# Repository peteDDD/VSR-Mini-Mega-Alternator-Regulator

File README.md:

# VSR-Mini-Mega-Rev-1

This project is a refactoring of the amazing work of William A. Thomason ("Al") to create an open source very smart alternator regulator.  That work can be seen here:
http://arduinoalternatorregulator.blogspot.com/

That open-source hardware is no longer orderable through Al.  In January 2019, that product "went pro" and is now available as a commercial product as you can see here:
http://wakespeed.com/products.html

In December 2020 I began refactoring Al's code to remove CAN and Bluetooth related code and move the hardware to a new PC board with a Mini Mega Pro 2560 daughter card
as the processor. Thus "VSR MINI MEGA" was born.

I wanted to remove some functionality and add other functionality.  Also, moving to the Mini Mega Pro 2560 provided more memory for expansion.

New hardware features include:
  - Dual INA226 current voltage sensors (for Alternator and Battery)    * Al's designs supported a second shunt but required a separate battery monitor to implement 
      that very unique and powerful functionality.  THe VSR MINI MEGA directly support two shunts.
  - Three Feature-in Ports and Three Feature-out Ports (functionality and port assignments selectable in Config.h)  
  - Two serial port screw headers, separate from port used to USB programming, one can support external full function display 
       (A remote display based on an Arduino Uno and a TFT color display will be published in the near future)
  - Two I2C pin headers to add an in-case OLED display or other features
  - Red and green LED output connections (independent of the Feature-out option which preceeded it).  
 
New firmware features include, selectable and configurable in Config.h include  :  
  - ENABLE_FEATURE_IN_SCUBA  - uses one of the Feature-in ports to shift the alternator field PWM way down so a small engine can run a SCUBA compressor while maintaining a 
      bit of output for keeping up with an electric clutch and relays used by the SCUBA compressor.
 -  FEATURE_OUT_GREEN_LED, FEATURE_OUT_RED_LED - echo the red and green status LED to your choice of Feature-out ports.
 -  FEATURE_OUT_LIFEPO_SHUTDOWN_ALARM - provides a Feature-out alarm which follows the Force-o-Float Feature-in
 -  USE_OLED - provides a class-based OLED display which displays realtime alternator and battery voltage, current, and temperatures, field PWM, current charging mode, 
      time in that mode, flags like "Forced Float" and "SCUBA", and error messages.  The display also reflects the DIP switch settings in human-speak at boot up.
 -  USE_SERIAL_DISPLAY - supports Arduio Uno-based color TFT display which alternately displays a screen showing alternator amps and battery voltage and a graphical display
      of the actual charging curve (amps and volts) over time
      
Features and firmware removed include (as best I can so far)
 -  CAN support
 -  Bluetooth artifacts from earlier VSR versions
 -  Engine control artifacts from Al's 6HP 12V diesel genset/water maker which preceded the VSR alternator regulator.
 -  Remote battery monitor artifacts
 
Future (near-term) enhancements planned:
 -  There is a stub in this release to support monitoring LiFePO4 battery management system's output for a pending battery disconnect.  This will then trigger a "Force-to-float"
      on the Mini-Mega to protect the alternator from a battery disconnect.
      
Also developed:
 -  Bench testing board to mimic battery and alternator voltages, currents, and temperatures, and feature-in and feature-out functions (switches and LEDs respectively)  
      This board also can have small volt and current meters on it and bannana jacks for stator input (from a signal generator) and tach out (to a frequency counter or 
      oscilloscope.
 -  The previously-mentioned remote color graphical display
 -  3D-printed case for VSR Mega-Mini with 0.93" OLED
 -  3D-printed bezel for the remote color graphical display

 FULL REFERENCE MANUAL CAN BE FOUND IN THE DOCUMENTATION DIRECTORY.
 
 ###

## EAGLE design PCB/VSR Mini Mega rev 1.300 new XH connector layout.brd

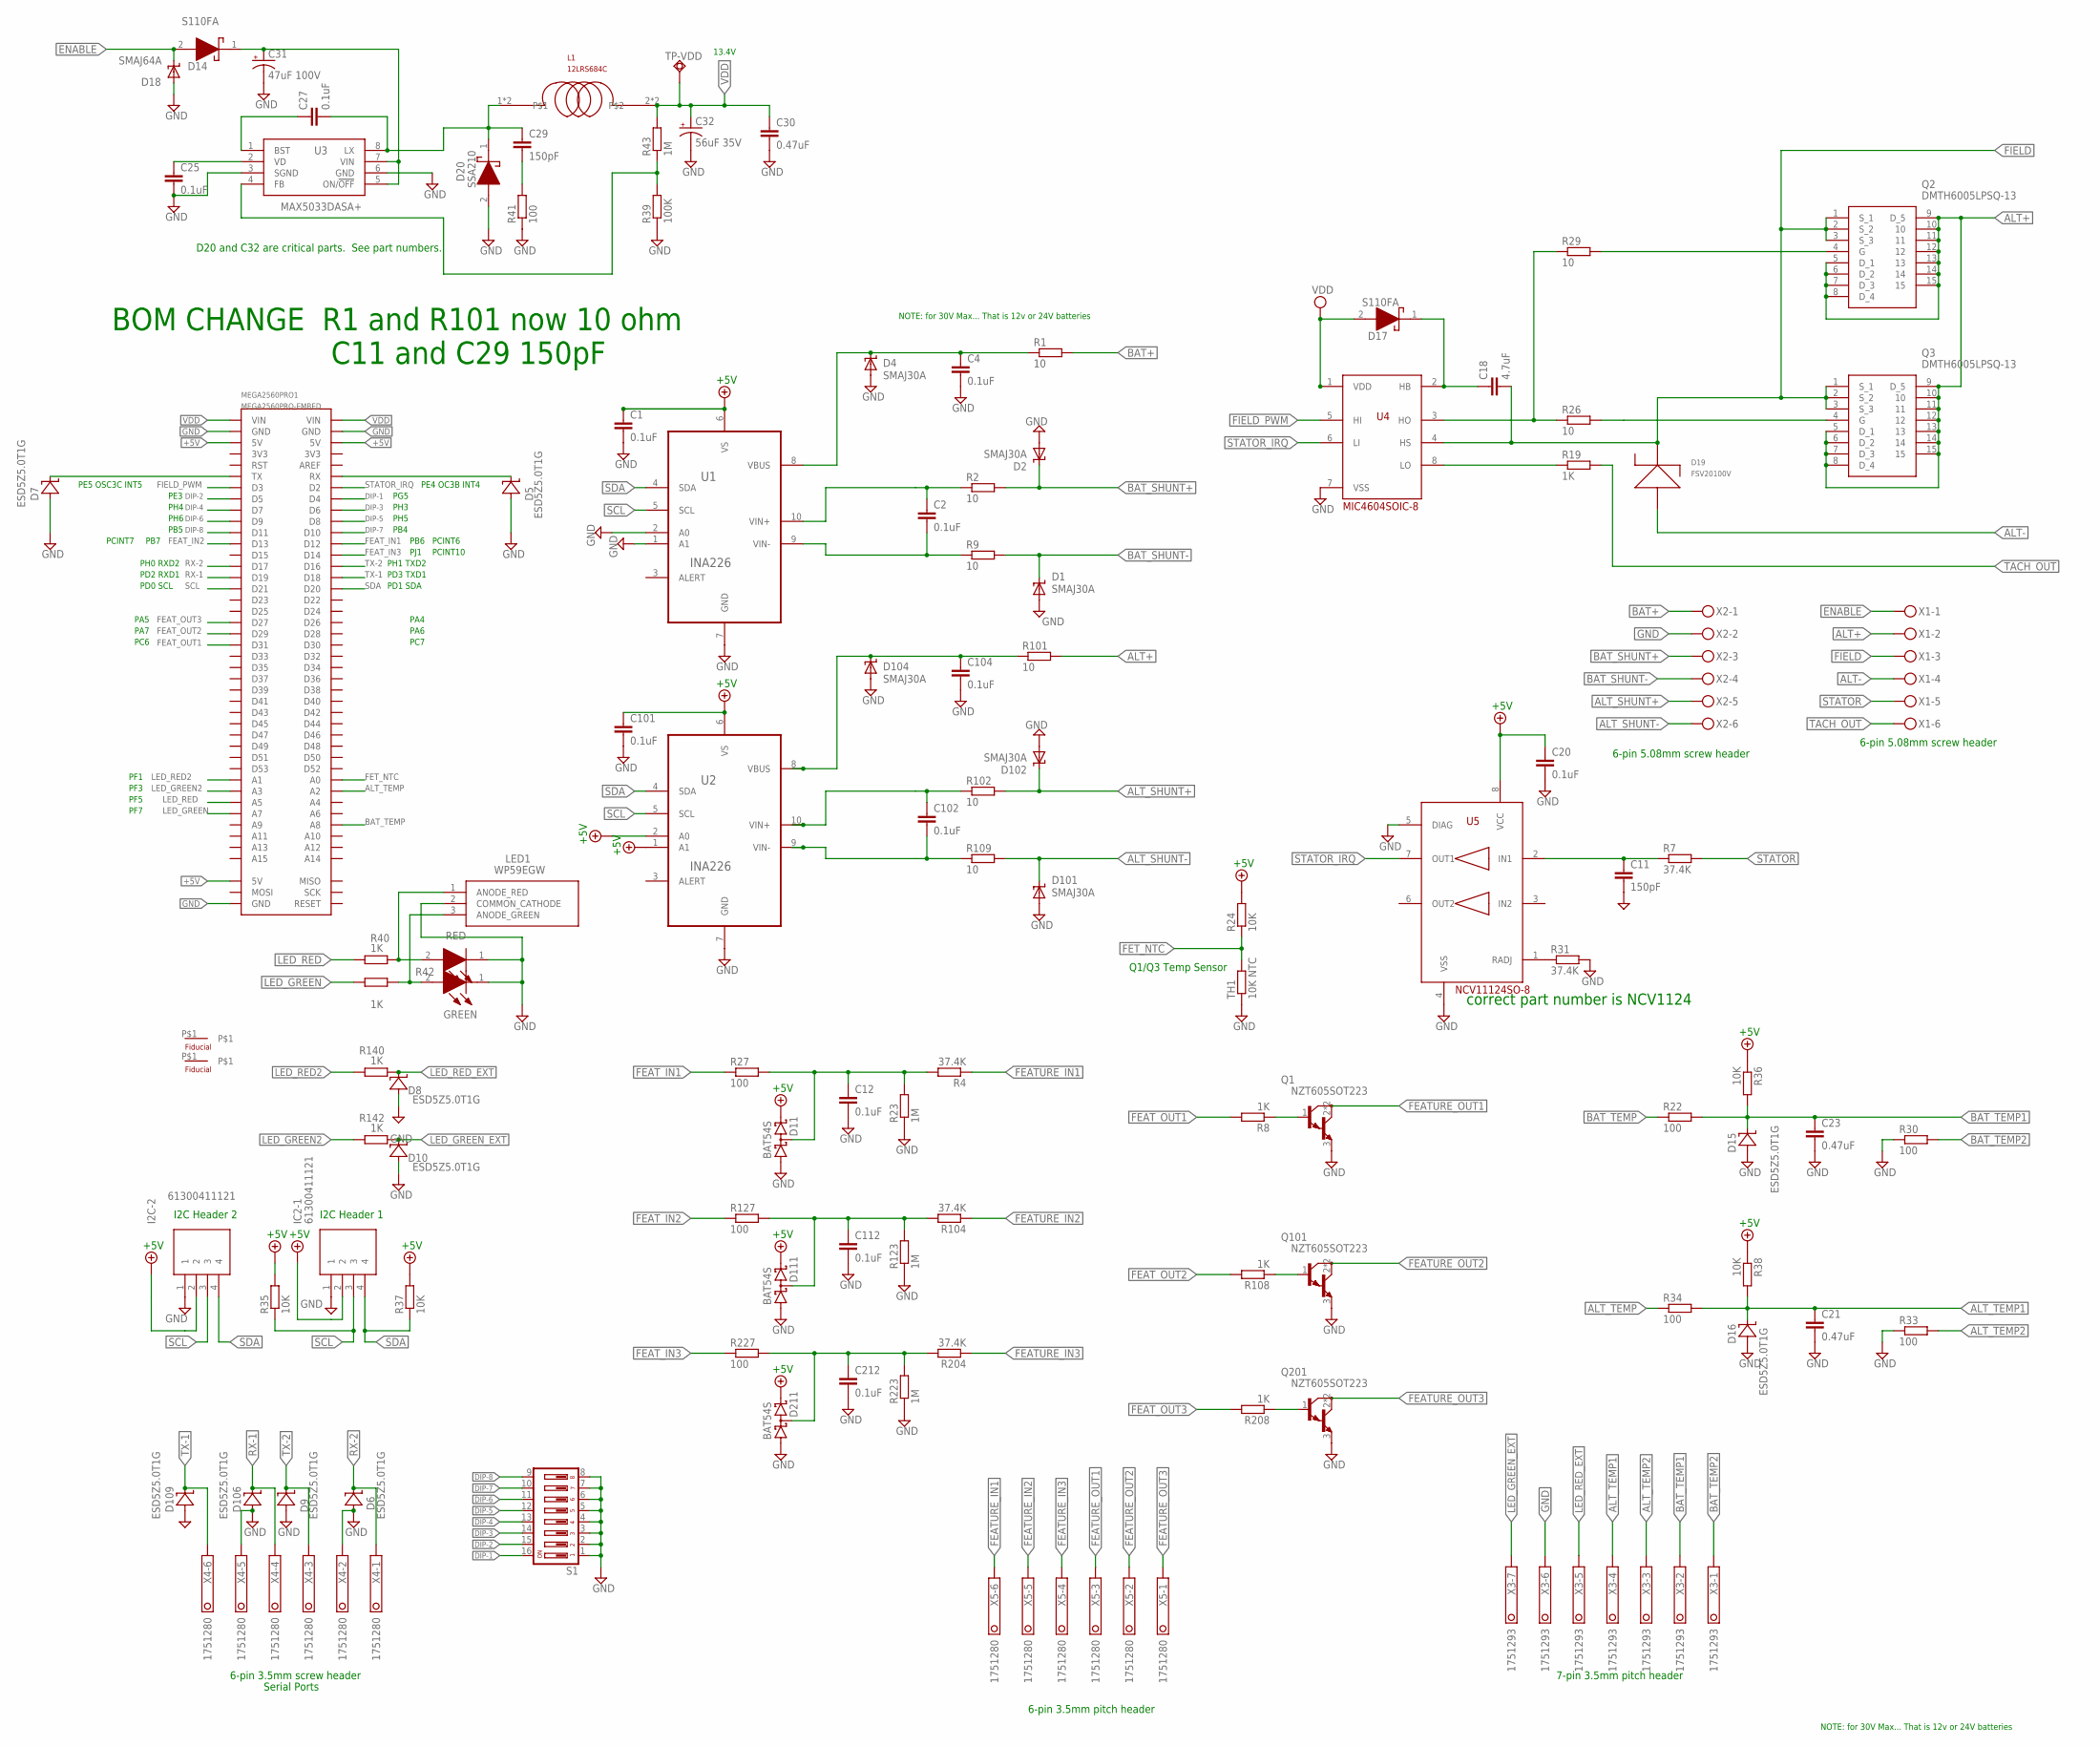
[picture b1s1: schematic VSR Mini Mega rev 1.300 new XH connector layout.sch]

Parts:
C1, C2, C4, C12, C20, C25, C27, C101, C102, C104, C112, C212: 0.1uF; C0603
C11, C29: 150pF; C0603
C18: 4.7uF; C0603K
C21, C23, C30: 0.47uF; C0603
C31: 47uF 100V; CAPPRD500W60D1000H1250B
C32: 56uF 35V; CAPPRD250W50D630H1100B
D1, D2, D4, D101, D102, D104: SMAJ30A; SMBJ
D5, D6, D7, D8, D9, D10, D15, D16, D106, D109: ESD5Z5.0T1G; SOD523
D11, D111, D211: BAT54S; SOT23
D14, D17: S110FA; SODFL3618X143N
D18: SMAJ64A; SMBJ
D19: FSV20100V; TO-277
D20: SSA210; DIOM5227X270N
FIDUCIAL1, FIDUCIAL2: FIDUCIAL060
GREEN: 599-0110-007F; LEDM2012X90N
I2C-2: 61300411121; HDRV4W95P0X254_1X4_1016X254X85
IC2-1: 61300411121; HDRV4W95P0X254_1X4_1016X254X85
L1: 12LRS684C; IND_12LRS156C
LED1: WP59EGW; T-1_3/4(5MM)_BI-COLOR_INDICATO
MEGA2560PRO1: MEGA2560PRO-EMBED
Q1, Q101, Q201: NZT605SOT223; SOT223
Q2, Q3: DMTH6005LPSQ-13; DMTH6005LPSQ13
R1, R2, R9, R26, R29, R101, R102, R109: 10; R0603
R4, R7, R31, R104, R204: 37.4K; R0603
R8, R19, R40, R42, R108, R140, R142, R208: 1K; R0603
R22, R27, R30, R33, R34, R41, R127, R227: 100; R0603
R23, R43, R123, R223: 1M; R0603
R24, R35, R36, R37, R38: 10K; R0603
R39: 100K; R0603
RED: 599-0110-007F; LEDM2012X90N
S1: DP08; DP-08
TH1: 10K NTC; R0402
TP-VDD: TPSQTP20SQ; TP20SQ
U1, U2: INA226; SOP50P490X110-10N
U3: MAX5033DASA+; SOIC127P600X175-8N
U4: MIC4604SOIC-8; SOIC8
U5: NCV11124SO-8; SO-8
X1, X2: MKDSN1,5/6-5,08
X3: 1751293
X4, X5: 1751280

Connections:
+5V: C1.1, C20.1, C101.1, D11.2 (C2), D111.2 (C2), D211.2 (C2), I2C-2.2, IC2-1.2, MEGA2560PRO1.5V@1 (5V), MEGA2560PRO1.5V@2 (5V), MEGA2560PRO1.5V@3 (5V), R24.2, R35.2, R36.1, R37.2, R38.1, U1.6 (VS), U2.1 (A1), U2.2 (A0), U2.6 (VS), U5.8 (VCC)
ALT+: Q2.5 (D_1), Q2.6 (D_2), Q2.7 (D_3), Q2.8 (D_4), Q2.9 (D_5), Q2.10, Q2.11, Q2.12, Q2.13, Q2.14, Q2.15, Q3.5 (D_1), Q3.6 (D_2), Q3.7 (D_3), Q3.8 (D_4), Q3.9 (D_5), Q3.10, Q3.11, Q3.12, Q3.13, Q3.14, Q3.15, R101.2, X1.2
ALT-: D19.1, D19.2, X1.4
ALT_SHUNT+: D102.C, R102.2, X2.5
ALT_SHUNT-: D101.C, R109.2, X2.6
ALT_TEMP: MEGA2560PRO1.A2, R34.1
ALT_TEMP1: C21.1, D16.C, R34.2, R38.2, X3.4
ALT_TEMP2: R33.2, X3.3
BAT+: R1.2, X2.1
BAT_SHUNT+: D2.C, R2.2, X2.3
BAT_SHUNT-: D1.C, R9.2, X2.4
BAT_TEMP: MEGA2560PRO1.A8, R22.1
BAT_TEMP1: C23.1, D15.C, R22.2, R36.2, X3.2
BAT_TEMP2: R30.2, X3.1
D111: C112.1, D111.3 (C1A2), R104.2, R123.2, R127.2
DIP-1: MEGA2560PRO1.D4, S1.16
DIP-2: MEGA2560PRO1.D5, S1.15
DIP-3: MEGA2560PRO1.D6, S1.14
DIP-4: MEGA2560PRO1.D7, S1.13
DIP-5: MEGA2560PRO1.D8, S1.12
DIP-6: MEGA2560PRO1.D9, S1.11
DIP-7: MEGA2560PRO1.D10, S1.10
DIP-8: MEGA2560PRO1.D11, S1.9
ENABLE: D14.2 (A), D18.C, X1.1
FEATURE_IN1: R4.1, X5.6
FEATURE_IN2: R104.1, X5.5
FEATURE_IN3: R204.1, X5.4
FEATURE_OUT1: Q1.2 (C), Q1.4 (C), X5.3
FEATURE_OUT2: Q101.2 (C), Q101.4 (C), X5.2
FEATURE_OUT3: Q201.2 (C), Q201.4 (C), X5.1
FEAT_IN1: MEGA2560PRO1.D12, R27.1
FEAT_IN2: MEGA2560PRO1.D13, R127.1
FEAT_IN3: MEGA2560PRO1.D14, R227.1
FEAT_OUT1: MEGA2560PRO1.D31, R8.2
FEAT_OUT2: MEGA2560PRO1.D29, R108.2
FEAT_OUT3: MEGA2560PRO1.D27, R208.2
FET_NTC: MEGA2560PRO1.A0, R24.1, TH1.2
FIELD: C18.2, D19.3, Q2.1 (S_1), Q2.2 (S_2), Q2.3 (S_3), Q3.1 (S_1), Q3.2 (S_2), Q3.3 (S_3), U4.4 (HS), X1.3
FIELD_PWM: MEGA2560PRO1.D3, U4.5 (HI)
GND: C1.2, C4.2, C11.2, C12.2, C20.2, C21.2, C23.2, C25.2, C30.2, C31.2 (-), C32.2 (-), C101.2, C104.2, C112.2, C212.2, D1.A, D2.A, D4.A, D5.A, D6.A, D7.A, D8.A, D9.A, D10.A, D11.1 (A1), D15.A, D16.A, D18.A, D20.2 (A), D101.A, D102.A, D104.A, D106.A, D109.A, D111.1 (A1), D211.1 (A1), GREEN.1 (K), I2C-2.1, IC2-1.1, LED1.2 (COMMON_CATHODE), MEGA2560PRO1.GND@1 (GND), MEGA2560PRO1.GND@2 (GND), MEGA2560PRO1.GND@3 (GND), Q1.3 (E), Q101.3 (E), Q201.3 (E), R23.1, R30.1, R31.2, R33.1, R39.1, R41.1, R123.1, R223.1, RED.1 (K), S1.1, S1.2, S1.3, S1.4, S1.5, S1.6, S1.7, S1.8, TH1.1, U1.1 (A1), U1.2 (A0), U1.7 (GND), U2.7 (GND), U3.3 (SGND), U3.6 (GND), U4.7 (VSS), U5.4 (VSS), U5.5 (DIAG), X2.2, X3.6, X4.2, X4.5
LED_GREEN: MEGA2560PRO1.A7, R42.1
LED_GREEN2: MEGA2560PRO1.A3, R142.1
LED_GREEN_EXT: D10.C, R142.2, X3.7
LED_RED: MEGA2560PRO1.A5, R40.1
LED_RED2: MEGA2560PRO1.A1, R140.1
LED_RED_EXT: D8.C, R140.2, X3.5
unnamed: C102.1, R102.1, U2.10 (VIN+)
unnamed: C102.2, R109.1, U2.9 (VIN-)
unnamed: C2.1, R2.1, U1.10 (VIN+)
unnamed: C2.2, R9.1, U1.9 (VIN-)
unnamed: C104.1, D104.C, R101.1, U2.8 (VBUS)
unnamed: C18.1, D17.1 (K), U4.2 (HB)
unnamed: C12.1, D11.3 (C1A2), R4.2, R23.2, R27.2
unnamed: R26.1, R29.1, U4.3 (HO)
unnamed: C212.1, D211.3 (C1A2), R204.2, R223.2, R227.2
unnamed: Q1.1 (B), R8.1
unnamed: Q2.4 (G), R29.2
unnamed: R19.1, U4.8 (LO)
unnamed: Q3.4 (G), R26.2
unnamed: C11.1, R7.1, U5.2 (IN1)
unnamed: R31.1, U5.1 (RADJ)
unnamed: Q101.1 (B), R108.1
unnamed: C4.1, D4.C, R1.1, U1.8 (VBUS)
unnamed: Q201.1 (B), R208.1
unnamed: C31.1 (+), D14.1 (K), U3.5 (ON/!OFF), U3.7 (VIN)
unnamed: C25.1, U3.2 (VD)
unnamed: C27.1, U3.1 (BST)
unnamed: C27.2, C29.1, D20.1 (K), L1.1, L1.4, U3.8 (LX)
unnamed: D7.C, MEGA2560PRO1.TX
unnamed: C29.2, R41.2
unnamed: LED1.1 (ANODE_RED), R40.2, RED.2 (A)
unnamed: GREEN.2 (A), LED1.3 (ANODE_GREEN), R42.2
unnamed: R39.2, R43.1, U3.4 (FB)
unnamed: D5.C, MEGA2560PRO1.RX
RX-1: D106.C, MEGA2560PRO1.D19, X4.4
RX-2: D6.C, MEGA2560PRO1.D17, X4.1
SCL: I2C-2.3, IC2-1.3, MEGA2560PRO1.D21, R35.1, U1.5 (SCL), U2.5 (SCL)
SDA: I2C-2.4, IC2-1.4, MEGA2560PRO1.D20, R37.1, U1.4 (SDA), U2.4 (SDA)
STATOR: R7.2, X1.5
STATOR_IRQ: MEGA2560PRO1.D2, U4.6 (LI), U5.7 (OUT1)
TACH_OUT: R19.2, X1.6
TX-1: D109.C, MEGA2560PRO1.D18, X4.6
TX-2: D9.C, MEGA2560PRO1.D16, X4.3
VDD: C30.1, C32.1 (+), D17.2 (A), L1.2, L1.3, MEGA2560PRO1.VIN@1 (VIN), MEGA2560PRO1.VIN@2 (VIN), R43.2, TP-VDD.TP, U4.1 (VDD)

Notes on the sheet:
6-pin 3.5mm pitch header
Q1/Q3 Temp Sensor
I2C Header 1
I2C Header 2
6-pin 3.5mm screw header
Serial Ports
6-pin 5.08mm screw header
7-pin 3.5mm pitch header
D20 and C32 are critical parts. See part numbers.
PH0 RXD2
PH1 TXD2
PH5
PH6
PE5 OSC3C INT5
PE4 OC3B INT4
PD3 TXD1
PD2 RXD1
PD1 SDA
PD0 SCL
PB4
PC6
PC7
PB6
13.4V
PF1
PF3
PA5
PA7
PA4
PA6
PE3
PH3
PB5
PH4
NOTE: for 30V Max... That is 12v or 24V batteries
BOM CHANGE R1 and R101 now 10 ohm
PG5
PB7
PJ1
PCINT6

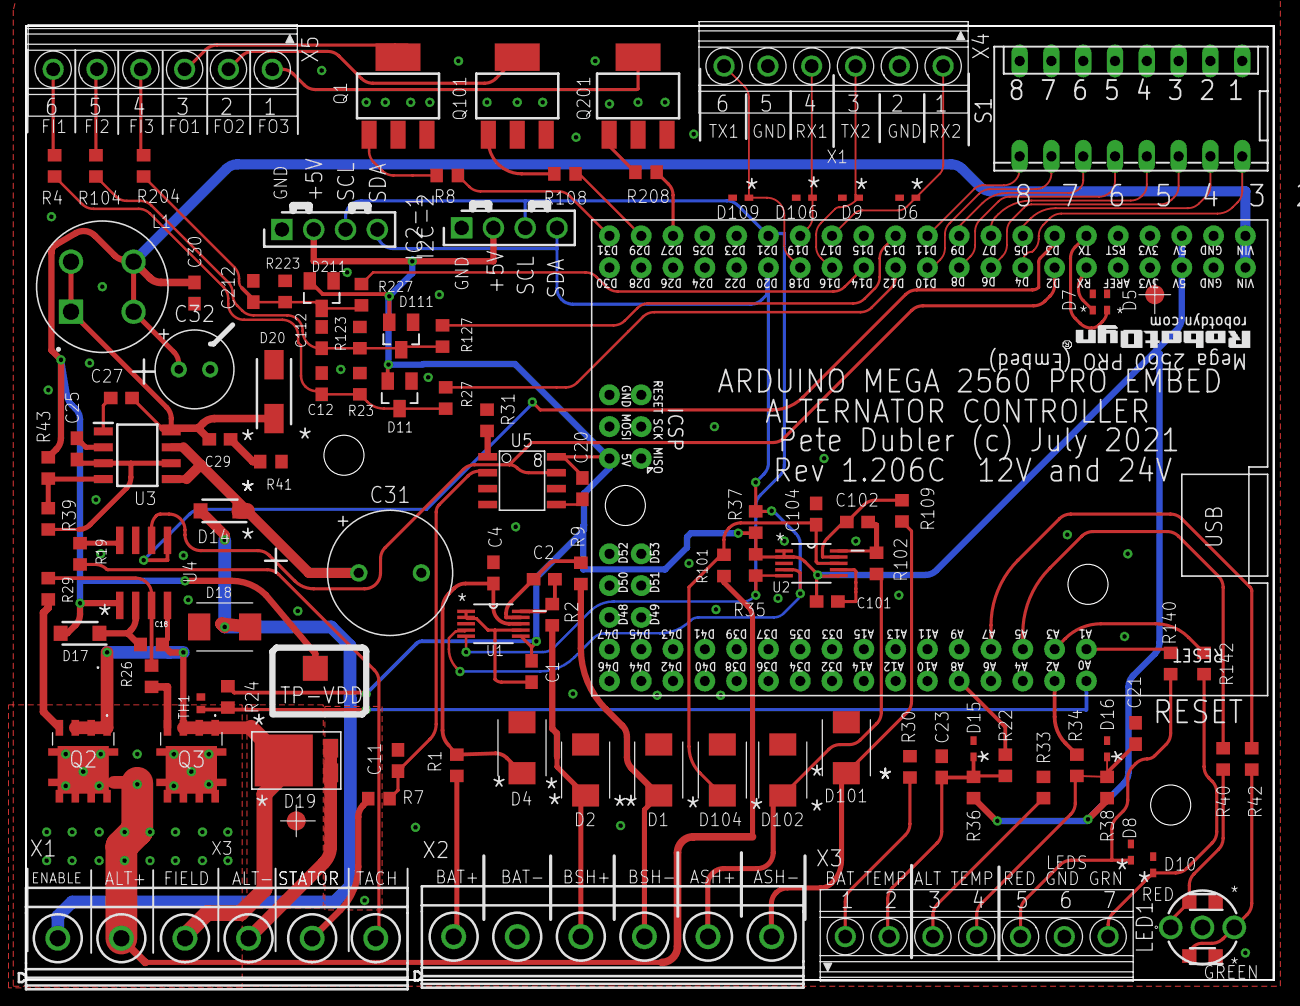
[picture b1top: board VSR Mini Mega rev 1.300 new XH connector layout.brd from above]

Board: 2 copper layers, 99.7 x 76.2 mm, 110 parts (0 on the bottom side), 84 nets.

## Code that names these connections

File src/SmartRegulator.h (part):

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  #define LED_RED_PCB A7 
#endif       
//
#define LED_GREEN_EXT A3    // Connected to status LED external connector.
#define LED_RED_EXT A1      // Connected to status LED external connector.
                              ////    #define CHARGE_PUMP_PORT                 6              // PWM port that drives the FET boost-voltage Charge Pump
#define SDA_PIN SDA
#define SCL_PIN SCL
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#define NTC_AVERAGING 30 //15 12/15/24 changed from 15 to 30  // There are up to 3 NTC sensors, and we will average 5 A/D samples each before converting to a temperature, to smooth things over. (Max 254) 
                         // Note that this, combined with SENSOR_SAMPLE_RATE will define how often the temperatures get updated...

#define STATOR_IRQ_NUMBER 4 // Stator IRQ is attached to arduino pin 2, INT-4, OSC3B, PE4

#define FIELD_PWM_PORT 3    // Field PWM is connected to arduino pin 3, PE5, OSC3C
#define set_PWM_frequency() TCCR3B = (TCCR3B & 0b11111000) | 0x04; // Set Timer 3 (Pin 2/3/5 PWM) to 122Hz (from default 488hz).  This more matches 
                                                                   // optimal Alternator Field requirements, as frequencies above 400Hz seem to send
                                                                   // ref: https://arduinoinfo.mywikis.net/wiki/Arduino-PWM-Frequency
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#define FAULT_BAT_VOLTS_LOW 8.0       // Anything below this means battery is damaged, or sensing wire is missing / failing.
#define FAULT_BAT_TEMP 60             //  At or above this, fault out. (Approx 140F)
#define FAULT_ALT_TEMP 1.15           //  Fault if Alt Temp exceeds desired set point by 10%  12/15/2024 - Changed to 1.15  15%
#define FAULT_FET_TEMP 70             // If Field driver FETs are over 80c (Approx 160f), something is wrong with the FETs - fault.

#define ADPT_ACPT_TIME_FACTOR 5 // If the regulators is operating in Adaptive Acceptance Duration mode (either because EXIT_ACPT_AMPS was set = -1, or                   
                                // if we are unable to measure any amps), the amount of time we spend in Bulk phase will be multiplied by this factor, and               
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// #define FIELD_PWM_MAX           -------              // Maximum alternator PWM value - (This is now defined in the CPU specific section of xxxx.h, SmartRegulator.h, SmartGen.h, etc...)
#define MAX_TACH_PWM 75  // Do not allow MIN PWM (held in 'thresholdPWMvalue') to go above this value when Tach Mode is enabled.  Safety, esp in case Auto tech mode is enabled. 
                         //  This same value is used to limit the highest value the user is allowed to enter using the $SCT ASCII command.
#define PWM_CHANGE_CAP 2 // Limits how much UP we will change the Field PWM in each time 'adjusting' it.

#define PWM_CHANGE_RATE 100UL // Time (in mS) between the 'adjustments' of the PWM.  Allows a settling period before making another move.

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#define LD3_THRESHOLD 0.100 // the PWM is pulled back.   Once these brute force changes are made, the normal PID engine can start 
                            // adjusting things back to the new situation.  PROTECT THE BATTERY IS #1 CRITERIA!!!!

#define LD1_PULLBACK 0.95 // On 1st sign of overvoltage, pull back the field a little.
#define LD2_PULLBACK 0.85 // On 2nd sign of overvoltage, pull back harder 
                          // LD 3 overvoltage holds the Field at 0 until the overvoltage situation clears.

#define AOT_PULLBACK_THRESHOLD 1.03 // If we find we are 3% over alternator temperature goal, the PID engine is not keeping up.
#define AOT_PULLBACK_RESUME 0.90    //  (And do not resume normal operation until we are at 90% of goal temperature or less)
#define AOT_PULLBACK_FACTOR 0.50    // Do something dramatic, cut field drive by 50% before it continues to rise and we fault out.

// Any time we go over-temp, it seems we have a condition
// of a fight between that temp value and the amp/watts target - creating an osculation situation.
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
// ----- Mainloop timing values, how often do we update the PWM, check for key pressed, etc.
//         All times are in mS
#define SENSOR_SAMPLE_RATE 100UL //50UL  12/15/24 changed from 50 to 100       // If we are not able to synchronize with the stator, force a sample of Volts, Amps, Temperatures, every 50mS min.
#define ACCUMULATE_SAMPLING_RATE 1000UL // Update the accumulated AHs and WHs  every 1 second.
#define SAMPLE_ALT_CAP_DURATION 10000UL // When we have decided it is time to sample the Alternators capability, run it hard for 10 seconds.
#define SAMPLE_ALT_CAP_REST 30000UL     // and give a 30 second minute rest period between Sampling Cycles.
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
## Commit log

2021-11-03 first release
2021-11-03 Add files via upload
    Added Reference Manual
2021-11-03 added note in readme about reference manual
2021-11-06 updating remote display
2021-11-06 Remote Display updated
2021-11-06 separated out remote display
2021-11-06 fixed missing ssd1306ascii library dependencies
2021-11-06 restored RST message in main.cpp
2021-11-06 removed dec 2020 remote display directory
2021-11-07 added both alt and bat shunt present tests and fault traps
2021-11-07 updated the DATE_CODE to 11/06/21
2021-12-26 Add files via upload
    In this version, I changed the pinout on the I2C XH connectors so the pins align with the typical 0.96" I2C OLED display board.
2021-12-26 Add files via upload
    added pdf of schematic
2024-06-15 061524 new oled display settings and 14.2 v
2024-06-15 061524 display and voltage settings
2024-06-24 062424 display changes
2024-06-25 062524 lunchtime
2024-06-25 062524 1515 display formatted through Fout
2024-06-25 062524 1600 all display working
2024-06-30 062924
2024-07-08 070824 genset and engine units programmed
2024-12-13 genset
2024-12-15 121524
2024-12-29 commit platformio
2024-12-29 in progress
2024-12-29 complete 12/29/24

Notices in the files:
src/SmartRegulator.h:
Copyright (c) 2018 by William A. Thomason. http://arduinoalternatorregulator.blogspot.com
Refactored 2020/2021 derivative work (c) 2021 by Pete Dubler
This program is free software: you can redistribute it and/or modify
it under the terms of the GNU General Public License as published by
the Free Software Foundation, either version 3 of the License, or
(at your option) any later version.
